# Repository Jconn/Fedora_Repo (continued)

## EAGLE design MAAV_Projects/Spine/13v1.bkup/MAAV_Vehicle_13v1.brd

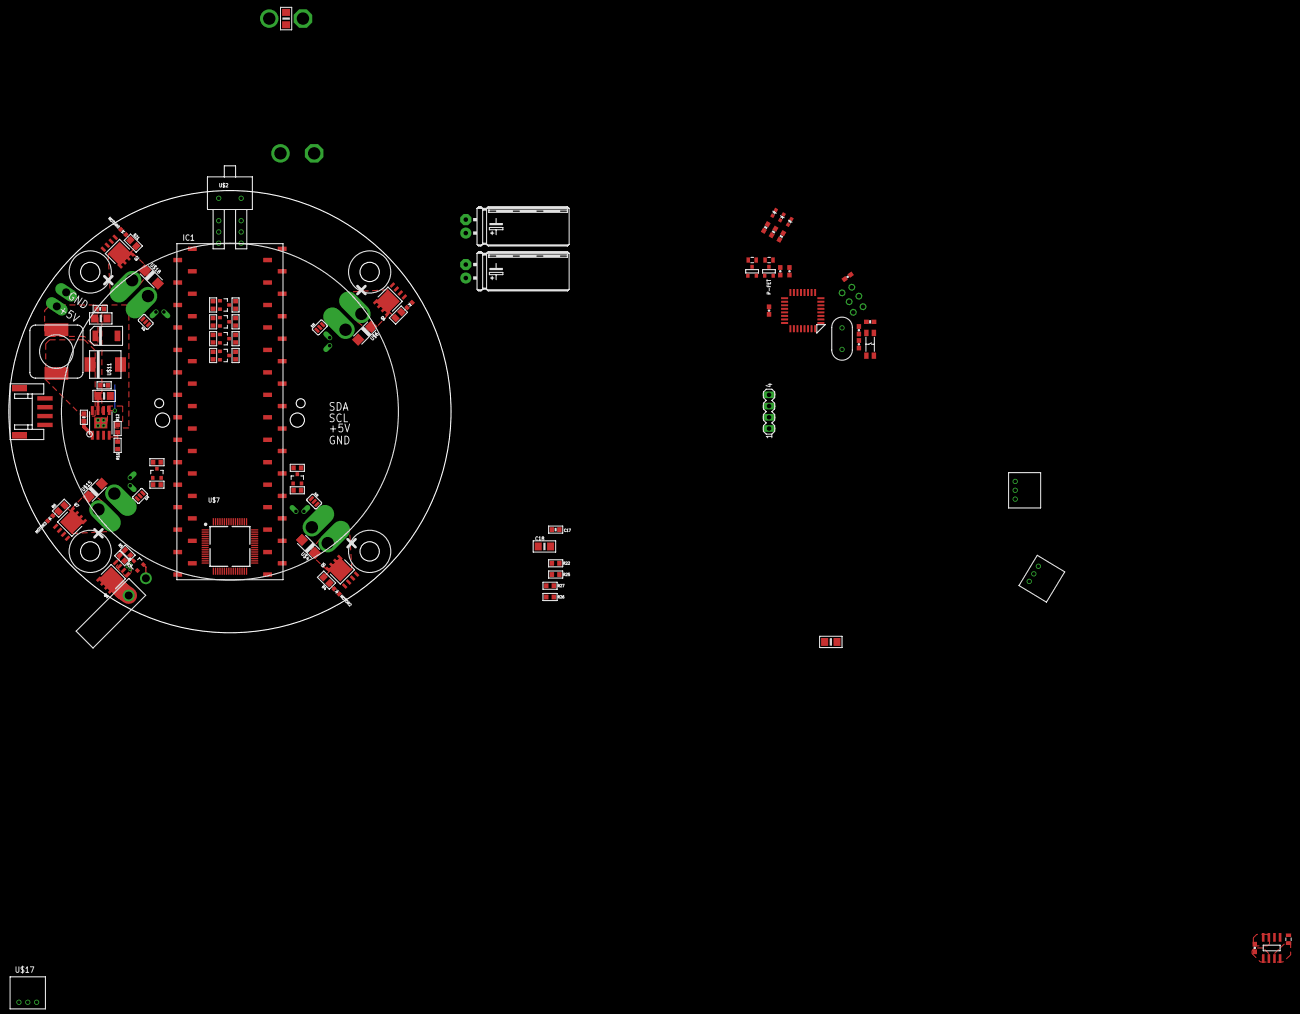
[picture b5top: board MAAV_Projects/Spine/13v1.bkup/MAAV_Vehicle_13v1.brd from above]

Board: 4 copper layers, 100.0 x 100.0 mm, 104 parts (1 on the bottom side), 60 nets.

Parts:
C2: C_2917_POL
C3, C6, C16: 0.01uF; C0603
C4, C5, C7, C18, C25: 10uF; C1206
C8: 10uF; 0805
C9: 10uF; 0603-CAP
C10, C11, C12, C13: 100nF; 0603-CAP
C14, C15: 22pF; 0603-CAP
C17: 0.1uF; C0603
C28, C29: 680uF; EH22-9
IC1: PINTO_SMD
IMU_LAYOUT: IMU
J1: MA03-2
J7: MA04-1; MA-04-SMD
LASER_POWER: POWER_CONN
LED1, LED2, LED3: GREEN; LED-0603
MOTOR0, MOTOR1, MOTOR2, MOTOR3: GREEN; CHIPLED_0603
MR1: SOT-23
Q1: CRYSTAL_16MHZ
Q2, Q4, Q5, Q6, Q7: SO-8_POWER-PAK
Q3: MOSFET-NCHANNELSMD; SOT23-3
R1, R2, R9, R10, R11, R13, R15, R17, R19, R22, R26: 10k; R0603
R3, R5: 1k; R0603
R4, R6, R21, R24: 750; R0805
R7: 10k; 0603-RES
R8, R23: 10k; 0805
R12: 3.16k; R0603
R14, R16, R18, R20: 4.7k; R0603
R25, R27: 432; R0603
R44, R47, R48: 240; 0603-RES
S2: SWITCH-OFF-MOM
SJ1, SJ2, SJ3, SJ4: SJ_3
SV1: MA04-1
T3, T4, T7, T8, T9, T10: MOSFET-NCHANNELSMD; SOT23-3
T11: SOT-23
U2: TPS5450
U3: ATMEGA328-AU; 32-TQFP
U4: REG_3V_8SOIC; 8-SOIC
U$1: INDUCTOR; CDRH127
U$2: SWITCH_DPDT; SWITCH_VERT_DPDT
U$3, U$5, U$13, U$14: ESC_CONN
U$4, U$6, U$15, U$18: DIODE-SCHOTTKY; DO-214AC,SMC
U$7: TM4C123GH6PM; 64-PQFP
U$8: LIPO_POWER
U$9: BATTERY50A; LIPO_POWER_50A
U$10, U$16, U$17: H3894-ND
U$11: DIODE-SCHOTTKYBIG; DO-214AB,SMC
U$12: POWER_HOLES

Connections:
+1V8: IC1.P24, IC1.P34, R1.2, R9.2, R13.2, R15.2, R17.2, R19.2, T3.1, T4.1, T7.1, T8.1, T9.1, T10.1
+5V: C2.A, C7.1, C9.1, C10.1, C11.1, C13.1, C16.1, C17.2, C18.2, IC1.P48, J1.P$6, J7.1, R2.2, R7.2, R10.2, R11.2, R14.2, R16.2, R18.2, R20.2, SV1.2, U3.P$4, U3.P$6, U3.P$18, U4.P$5, U4.P$6, U$1.P2, U$10.POW, U$12.P$1, U$16.POW, U$17.POW
+12V: C3.1, C4.1, C5.1, C25.1, C28.+, C29.+, Q2.S1, Q2.S2, Q2.S3, Q4.S1, Q4.S2, Q4.S3, Q5.S1, Q5.S2, Q5.S3, Q6.S1, Q6.S2, Q6.S3, Q7.S1, Q7.S2, Q7.S3, R3.2, R8.2, U2.P$7, U$2.P$3, U$9.BATT
-3V3: C8.1, U4.P$7, U4.P$8
BATT_SENSE: R26.1, R27.2, U3.P$19
ENABLE: MR1.2, Q3.1, R22.2, R26.2, U$2.P$2
GND: C2.C, C3.2, C4.2, C5.2, C7.2, C8.2, C9.2, C10.2, C11.2, C12.2, C13.2, C14.1, C15.1, C16.2, C17.1, C18.1, C25.2, C28.-, C29.-, IC1.P9, IC1.P23, IC1.P33, IC1.P45, J1.P$4, J7.4, LASER_POWER.P2, LED1.C, LED2.C, LED3.C, MOTOR0.C, MOTOR1.C, MOTOR2.C, MOTOR3.C, Q3.2, R12.2, R23.1, R25.1, R27.1, S2.P$2, S2.P$4, SV1.1, T11.2, U2.P$6, U2.P$9, U2.P$10, U2.P$11, U2.P$12, U2.P$13, U3.P$3, U3.P$5, U3.P$21, U4.P$3, U4.P$4, U$2.P$1, U$2.P$4, U$3.GND, U$4.A, U$5.GND, U$6.A, U$7.P$12, U$7.P$27, U$7.P$39, U$7.P$55, U$9.GND, U$10.GND, U$11.A, U$12.P$2, U$13.GND, U$14.GND, U$15.A, U$16.GND, U$17.GND, U$18.A
KILL_SIG: U3.P$12, U$17.SIG
LED1: R48.2, U3.P$13
LED2: R47.2, U3.P$26
LED3: R44.2, U3.P$2
M0_POWER: Q2.D1, Q2.D2, Q2.D3, Q2.D4, Q2.D5, R21.2, U$13.BATT, U$18.C
M1_POWER: Q6.D1, Q6.D2, Q6.D3, Q6.D4, Q6.D5, R24.2, U$5.BATT, U$6.C
M2_POWER: Q5.D1, Q5.D2, Q5.D3, Q5.D4, Q5.D5, R4.2, U$3.BATT, U$4.C
M3_POWER: Q7.D1, Q7.D2, Q7.D3, Q7.D4, Q7.D5, R6.2, U$14.BATT, U$15.C
MISO: J1.P$1, U3.P$16
MOSI: J1.P$5, U3.P$15
MOTOR0_PWM_1V8: IC1.P38, R13.1, T7.2
MOTOR0_PWM_5V: R14.1, SJ1.3, T7.3
MOTOR1_PWM_1V8: IC1.P36, R15.1, T8.2
MOTOR1_PWM_5V: R16.1, SJ3.3, T8.3
MOTOR2_PWM_1V8: IC1.P35, R17.1, T9.2
MOTOR2_PWM_5V: R18.1, SJ2.3, T9.3
MOTOR3_PWM_1V8: IC1.P37, R19.1, T10.2
MOTOR3_PWM_5V: R20.1, SJ4.3, T10.3
MOTOR_ENABLE: MR1.1, Q2.G, Q5.G, Q6.G, Q7.G, R23.2
MOTOR_LOGIC: T11.3, U3.P$11
unnamed: Q4.G, R3.1, R5.2
unnamed: LED1.A, R44.1
unnamed: C12.1, U3.P$20
unnamed: R11.1, R12.1, U2.P$4
unnamed: MR1.3, R8.1, T11.1
unnamed: C14.2, Q1.P$2, U3.P$8
unnamed: C15.2, Q1.P$1, U3.P$7
unnamed: C6.1, U2.P$1
unnamed: Q3.3, R5.1
unnamed: U2.P$5, U$2.P$5, U$2.P$6
unnamed: MOTOR1.A, R24.1
unnamed: SJ1.2, U$13.SDA/C+
unnamed: MOTOR2.A, R4.1
unnamed: MOTOR3.A, R6.1
unnamed: SJ2.2, U$3.SDA/C+
unnamed: SJ3.2, U$5.SDA/C+
unnamed: SJ4.2, U$14.SDA/C+
unnamed: MOTOR0.A, R21.1
unnamed: C6.2, U2.P$8, U$1.P1, U$11.C
unnamed: LED2.A, R47.1
unnamed: LED3.A, R48.1
unnamed: LASER_POWER.P1, Q4.D1, Q4.D2, Q4.D3, Q4.D4, Q4.D5
unnamed: IC1.P47, R22.1, R25.2
OPT0_SIG: U3.P$23, U$16.SIG
OPT1_SIG: U3.P$1, U$10.SIG
RESET: J1.P$3, R7.1, S2.P$1, S2.P$3, U3.P$29
RXD1: IC1.P17, J7.3
SCK: J1.P$2, U3.P$17
SCL_1V8: IC1.P31, R1.1, T3.2
SCL_5V: R2.1, SV1.4, T3.3, U3.P$28, U$3.SCL/C-, U$5.SCL/C-, U$13.SCL/C-, U$14.SCL/C-
SDA_1V8: IC1.P32, R9.1, T4.2
SDA_5V: R10.1, SJ1.1, SJ2.1, SJ3.1, SJ4.1, SV1.3, T4.3, U3.P$27
TXD1: IC1.P18, J7.2

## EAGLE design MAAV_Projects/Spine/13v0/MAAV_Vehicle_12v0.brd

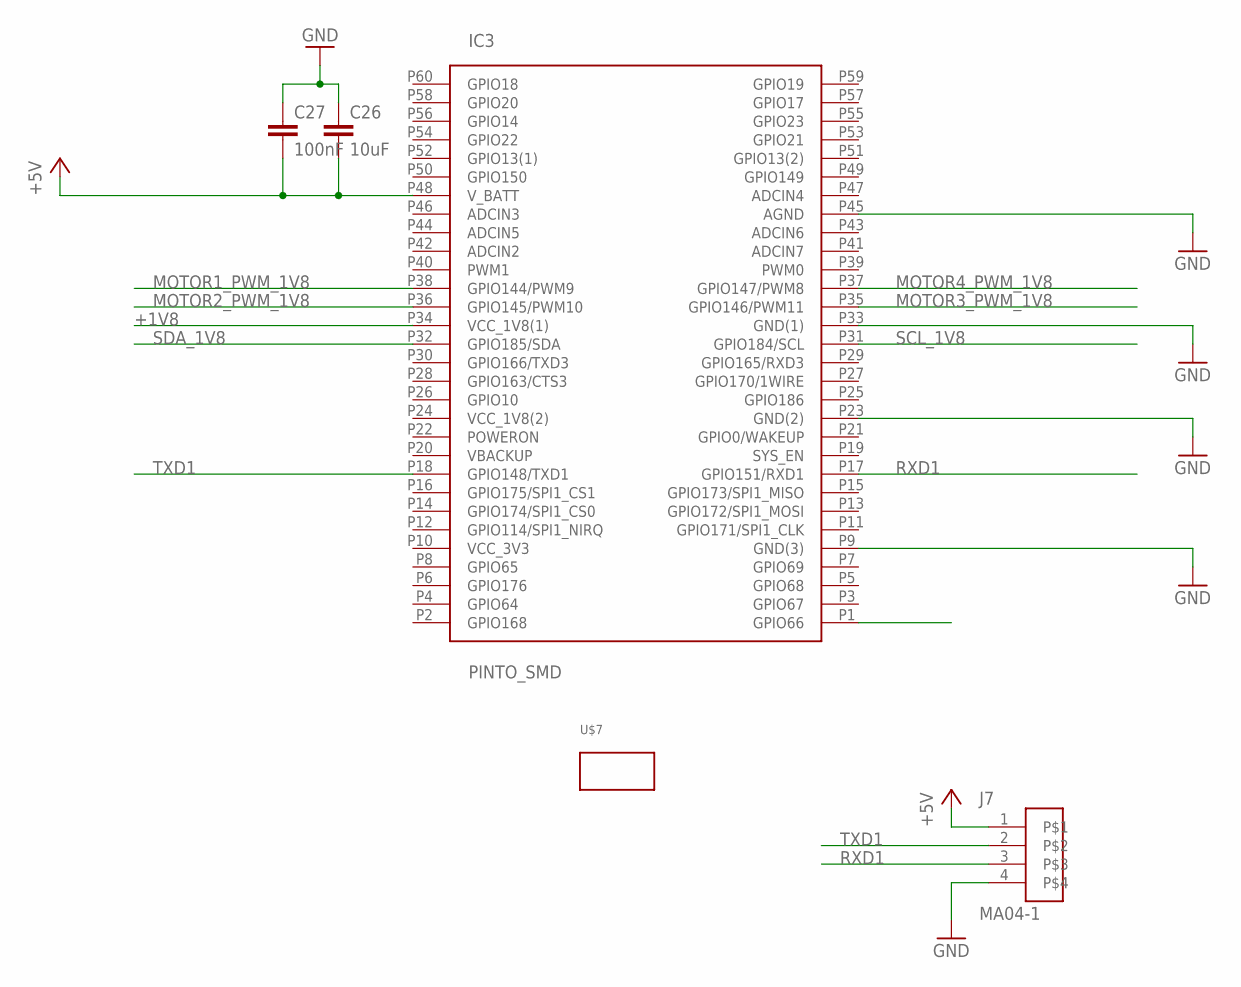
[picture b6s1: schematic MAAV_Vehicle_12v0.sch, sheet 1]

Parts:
C26: 10uF; 0603-CAP; DIGIKEY 445-4112-1-ND
C27: 100nF; 0603-CAP; DIGIKEY 478-1239-1-ND
IC3: PINTO_SMD; DIGIKEY S5641-ND (6)
J7: MA04-1; 455-1751-1-ND
U$7: IMU

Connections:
+1V8: IC3.P34 (VCC_1V8(1)); also elsewhere on the board
+5V: C26.2, C27.2, IC3.P48 (V_BATT), J7.1; also elsewhere on the board
GND: C26.1, C27.1, IC3.P9 (GND(3)), IC3.P23 (GND(2)), IC3.P33 (GND(1)), IC3.P45 (AGND), J7.4; also elsewhere on the board
MOTOR1_PWM_1V8: IC3.P38 (GPIO144/PWM9); also elsewhere on the board
MOTOR2_PWM_1V8: IC3.P36 (GPIO145/PWM10); also elsewhere on the board
MOTOR3_PWM_1V8: IC3.P35 (GPIO146/PWM11); also elsewhere on the board
MOTOR4_PWM_1V8: IC3.P37 (GPIO147/PWM8); also elsewhere on the board
RXD1: IC3.P17 (GPIO151/RXD1), J7.3
SCL_1V8: IC3.P31 (GPIO184/SCL); also elsewhere on the board
SDA_1V8: IC3.P32 (GPIO185/SDA); also elsewhere on the board
TXD1: IC3.P18 (GPIO148/TXD1), J7.2

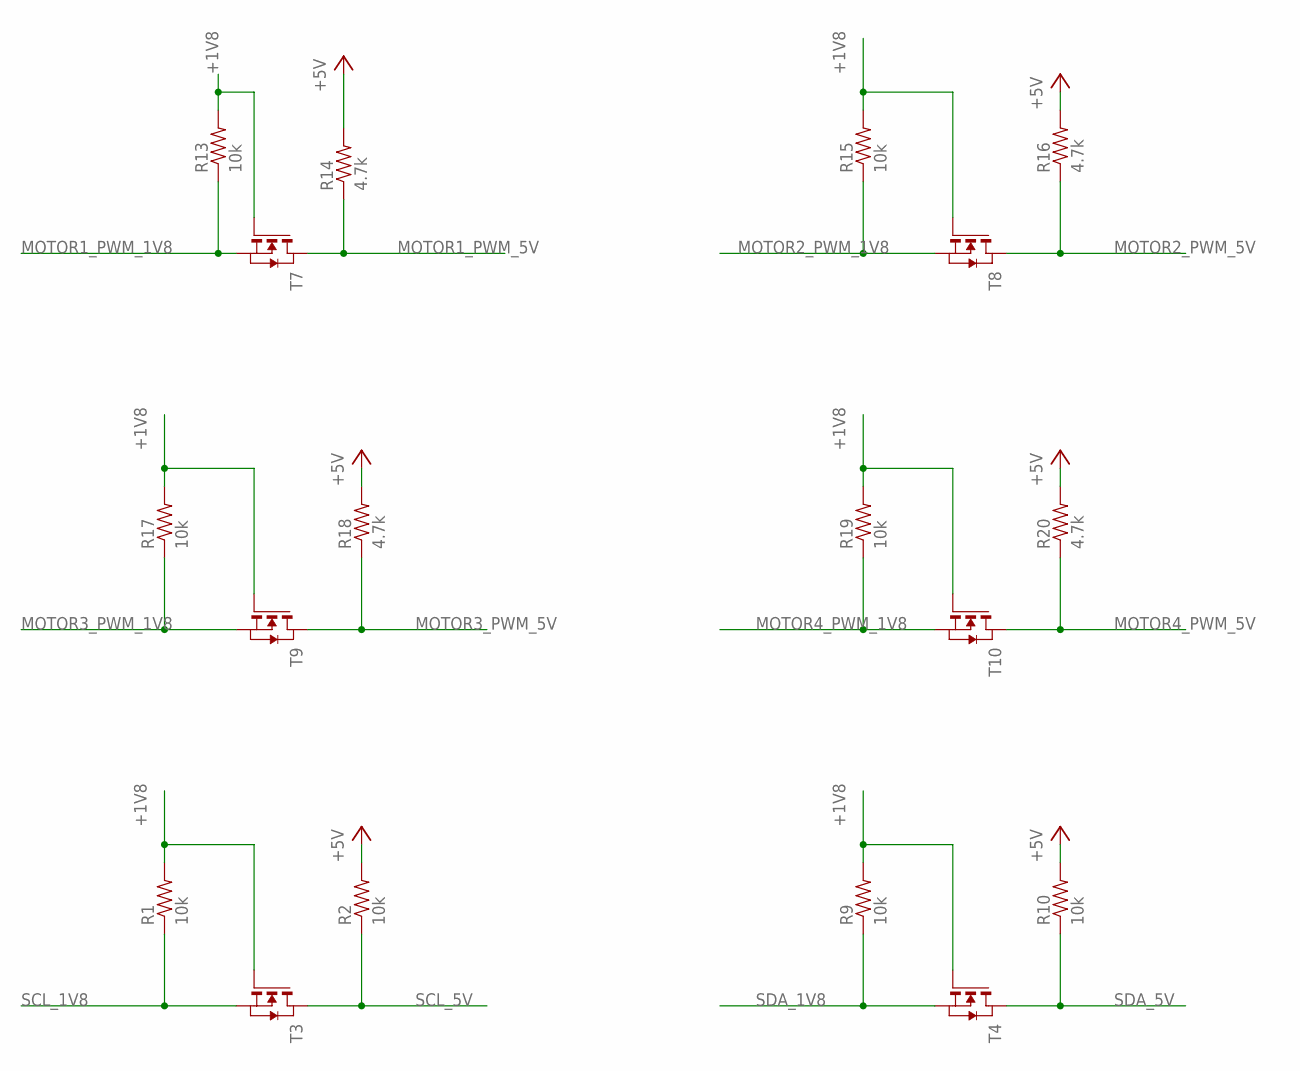
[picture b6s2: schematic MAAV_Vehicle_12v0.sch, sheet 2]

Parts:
R1, R2, R9, R10, R13, R15, R17, R19: 10k; 0603-RES; DIGIKEY P10KGCT-ND
R14, R16, R18, R20: 4.7k; 0603-RES; DIGIKEY P10KGCT-ND
T3, T4, T7, T8, T9, T10: NMOSSOT23; SOT-23; DIGIKEY BSS138KCT-ND

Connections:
+1V8: R1.2, R9.2, R13.2, R15.2, R17.2, R19.2, T3.3 (G), T4.3 (G), T7.3 (G), T8.3 (G), T9.3 (G), T10.3 (G); also elsewhere on the board
+5V: R2.2, R10.2, R14.2, R16.2, R18.2, R20.2; also elsewhere on the board
MOTOR1_PWM_1V8: R13.1, T7.2 (S); also elsewhere on the board
MOTOR1_PWM_5V: R14.1, T7.1 (D); also elsewhere on the board
MOTOR2_PWM_1V8: R15.1, T8.2 (S); also elsewhere on the board
MOTOR2_PWM_5V: R16.1, T8.1 (D); also elsewhere on the board
MOTOR3_PWM_1V8: R17.1, T9.2 (S); also elsewhere on the board
MOTOR3_PWM_5V: R18.1, T9.1 (D); also elsewhere on the board
MOTOR4_PWM_1V8: R19.1, T10.2 (S); also elsewhere on the board
MOTOR4_PWM_5V: R20.1, T10.1 (D); also elsewhere on the board
SCL_1V8: R1.1, T3.2 (S); also elsewhere on the board
SCL_5V: R2.1, T3.1 (D); also elsewhere on the board
SDA_1V8: R9.1, T4.2 (S); also elsewhere on the board
SDA_5V: R10.1, T4.1 (D); also elsewhere on the board

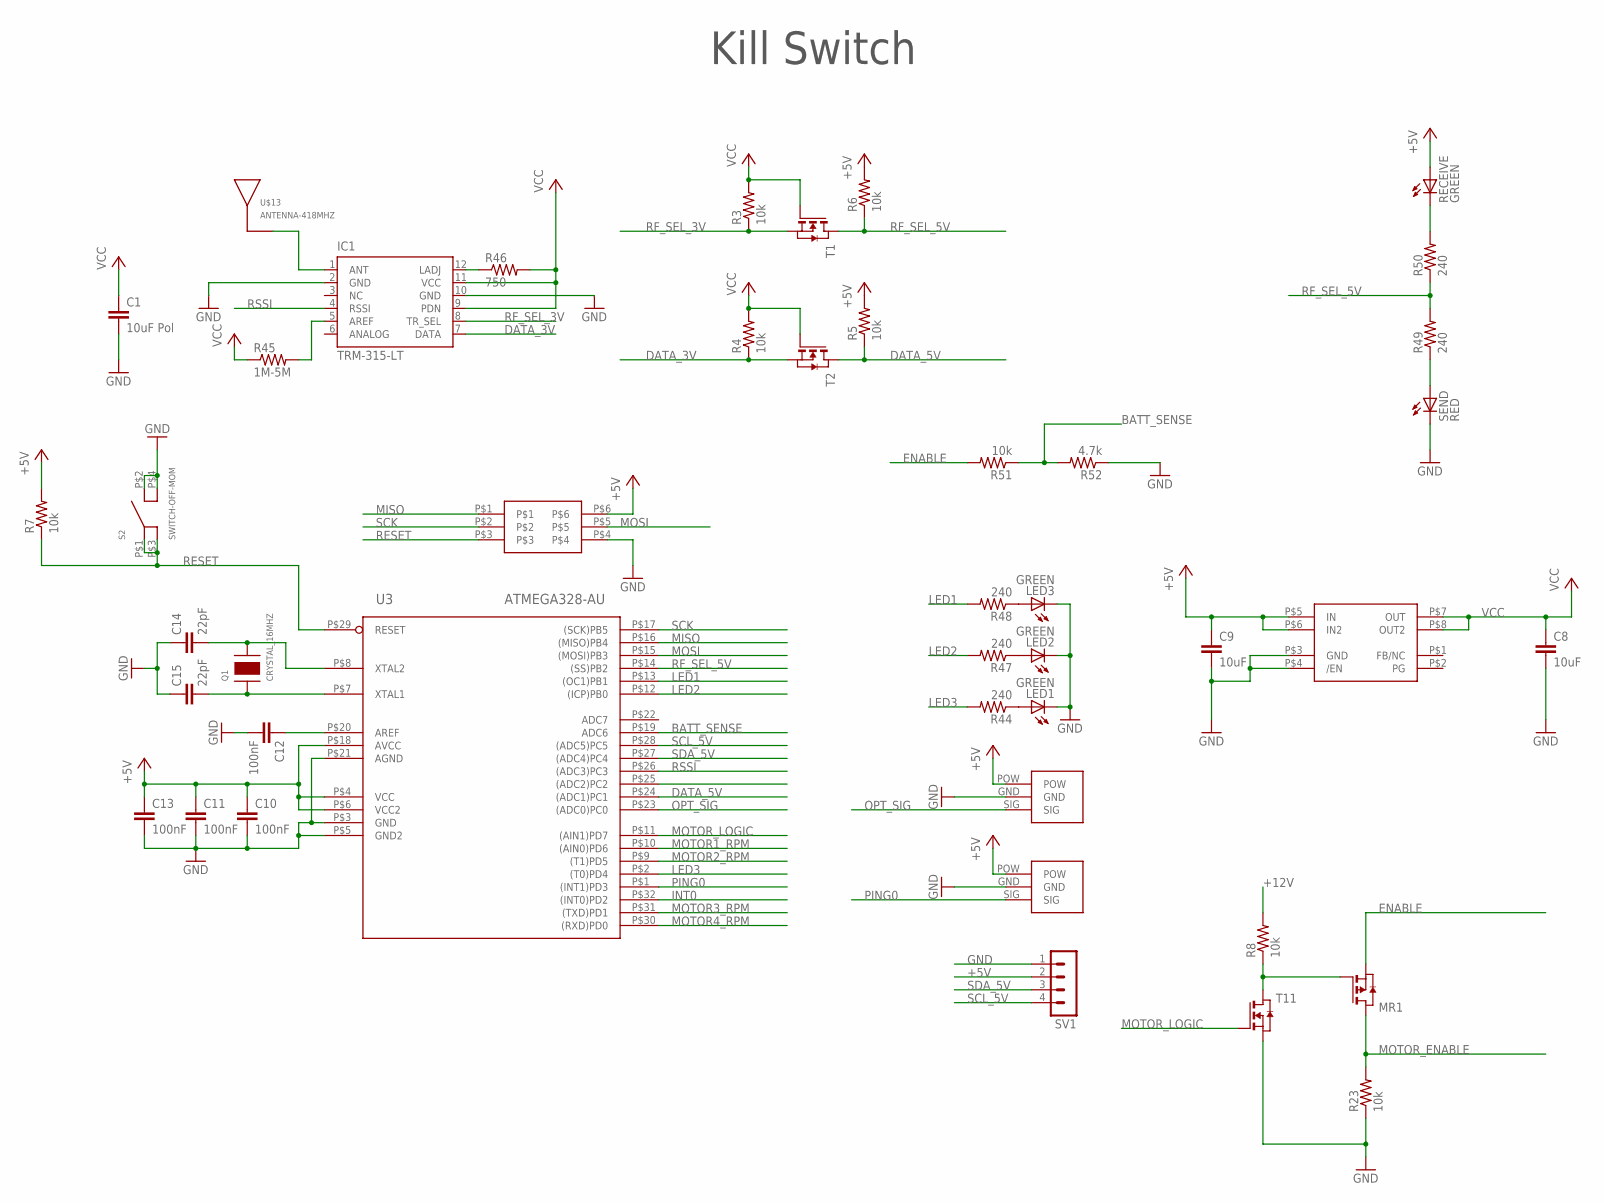
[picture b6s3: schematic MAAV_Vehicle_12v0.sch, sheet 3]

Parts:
C1: 10uF Pol; 0805; DIGIKEY 478-3273-1-ND
C8: 10uF; 0805; DIGIKEY 490-1746-1-ND
C9: 10uF; 0603-CAP; DIGIKEY 445-4112-1-ND
C10, C11, C12, C13: 100nF; 0603-CAP; DIGIKEY 478-1239-1-ND
C14, C15: 22pF; 0603-CAP; DIGIKEY 478-6200-1-ND
IC1: TRM-315-LT; TRM-XXX-LT; DIGIKEY TRM-315-LT-ND
J1: MA03-2
LED1, LED2, LED3: GREEN; LED-0603; DIGIKEY 1080-1405-1-ND
MR1: PMOSSOT23; SOT-23; DIGIKEY FDV304PCT-ND
Q1: CRYSTAL_16MHZ
R3, R4, R5, R6, R7: 10k; 0603-RES; DIGIKEY P10KGCT-ND
R8, R23: 10k; 0805; DIGIKEY P10KACT-ND
R44, R47, R48, R49, R50: 240; 0603-RES; DIGIKEY P240GCT-ND
R45: 1M-5M; 0603-RES; DIGIKEY P1.0MGCT-ND
R46: 750; 0603-RES; DIGIKEY P0.0GCT-ND
R51: 10k; 0603-RES; DIGIKEY P240GCT-ND
R52: 4.7k; 0603-RES; DIGIKEY P4.7KGCT-ND
RECEIVE: GREEN; LED-0603; DIGIKEY 1080-1405-1-ND
S2: SWITCH-OFF-MOM
SEND: RED; LED-0603; DIGIKEY 1080-1400-1-ND
SV1: MA04-1
T1, T2, T11: NMOSSOT23; SOT-23; DIGIKEY BSS138KCT-ND
U3: ATMEGA328-AU; 32-TQFP
U4: REG_3V_8SOIC; 8-SOIC
U$10, U$16: H3894-ND
U$13: ANTENNA-418MHZ

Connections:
+5V: C9.1, C10.1, C11.1, C13.1, J1.P$6, R5.2, R6.2, R7.2, RECEIVE.A, SV1.2, U3.P$4 (VCC), U3.P$6 (VCC2), U3.P$18 (AVCC), U4.P$5 (IN), U4.P$6 (IN2), U$10.POW, U$16.POW; also elsewhere on the board
+12V: R8.2; also elsewhere on the board
ANTENNA: IC1.1 (ANT), U$13.P$1; also elsewhere on the board
BATT_SENSE: R51.1, R52.2, U3.P$19 (ADC6)
DATA_3V: IC1.7 (DATA), R4.1, T2.2 (S)
DATA_5V: R5.1, T2.1 (D), U3.P$24 ((ADC1)PC1)
ENABLE: MR1.2 (S), R51.2; also elsewhere on the board
GND: C1.2, C8.2, C9.2, C10.2, C11.2, C12.2, C13.2, C14.1, C15.1, IC1.2 (GND), IC1.10 (GND), J1.P$4, LED1.C, LED2.C, LED3.C, R23.1, R52.1, S2.P$2 (P2), S2.P$4 (P4), SEND.C, SV1.1, T11.2 (S), U3.P$3 (GND), U3.P$5 (GND2), U3.P$21 (AGND), U4.P$3 (GND), U4.P$4 (/EN), U$10.GND, U$16.GND; also elsewhere on the board
INT0: U3.P$32 ((INT0)PD2); also elsewhere on the board
LED1: R48.2, U3.P$13 ((OC1)PB1)
LED2: R47.2, U3.P$12 ((ICP)PB0)
LED3: R44.2, U3.P$2 ((T0)PD4)
MISO: J1.P$1, U3.P$16 ((MISO)PB4); also elsewhere on the board
MOSI: J1.P$5, U3.P$15 ((MOSI)PB3); also elsewhere on the board
MOTOR1_RPM: U3.P$10 ((AIN0)PD6); also elsewhere on the board
MOTOR2_RPM: U3.P$9 ((T1)PD5); also elsewhere on the board
MOTOR3_RPM: U3.P$31 ((TXD)PD1); also elsewhere on the board
MOTOR4_RPM: U3.P$30 ((RXD)PD0); also elsewhere on the board
MOTOR_ENABLE: MR1.1 (D), R23.2; also elsewhere on the board
MOTOR_LOGIC: T11.3 (G), U3.P$11 ((AIN1)PD7)
unnamed: LED1.A, R44.1
unnamed: C12.1, U3.P$20 (AREF)
unnamed: MR1.3 (G), R8.1, T11.1 (D)
unnamed: C14.2, Q1.P$2, U3.P$8 (XTAL2)
unnamed: C15.2, Q1.P$1, U3.P$7 (XTAL1)
unnamed: R50.2, RECEIVE.C
unnamed: R49.1, SEND.A
unnamed: IC1.5 (AREF), R45.2
unnamed: IC1.12 (LADJ), R46.1
unnamed: LED2.A, R47.1
unnamed: LED3.A, R48.1
OPT_SIG: U3.P$23 ((ADC0)PC0), U$16.SIG
PING0: U3.P$1 ((INT1)PD3), U$10.SIG
RESET: J1.P$3, R7.1, S2.P$1 (P1), S2.P$3 (P3), U3.P$29 (RESET)
RF_SEL_3V: IC1.8 (TR_SEL), R3.1, T1.2 (S)
RF_SEL_5V: R6.1, R49.2, R50.1, T1.1 (D), U3.P$14 ((SS)PB2); also elsewhere on the board
RSSI: IC1.4 (RSSI), U3.P$26 ((ADC3)PC3)
SCK: J1.P$2, U3.P$17 ((SCK)PB5); also elsewhere on the board
SCL_5V: SV1.4, U3.P$28 ((ADC5)PC5); also elsewhere on the board
SDA_5V: SV1.3, U3.P$27 ((ADC4)PC4); also elsewhere on the board
VCC: C1.1, C8.1, IC1.9 (PDN), IC1.11 (VCC), R3.2, R4.2, R45.1, R46.2, T1.3 (G), T2.3 (G), U4.P$7 (OUT), U4.P$8 (OUT2)

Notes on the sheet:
Kill Switch

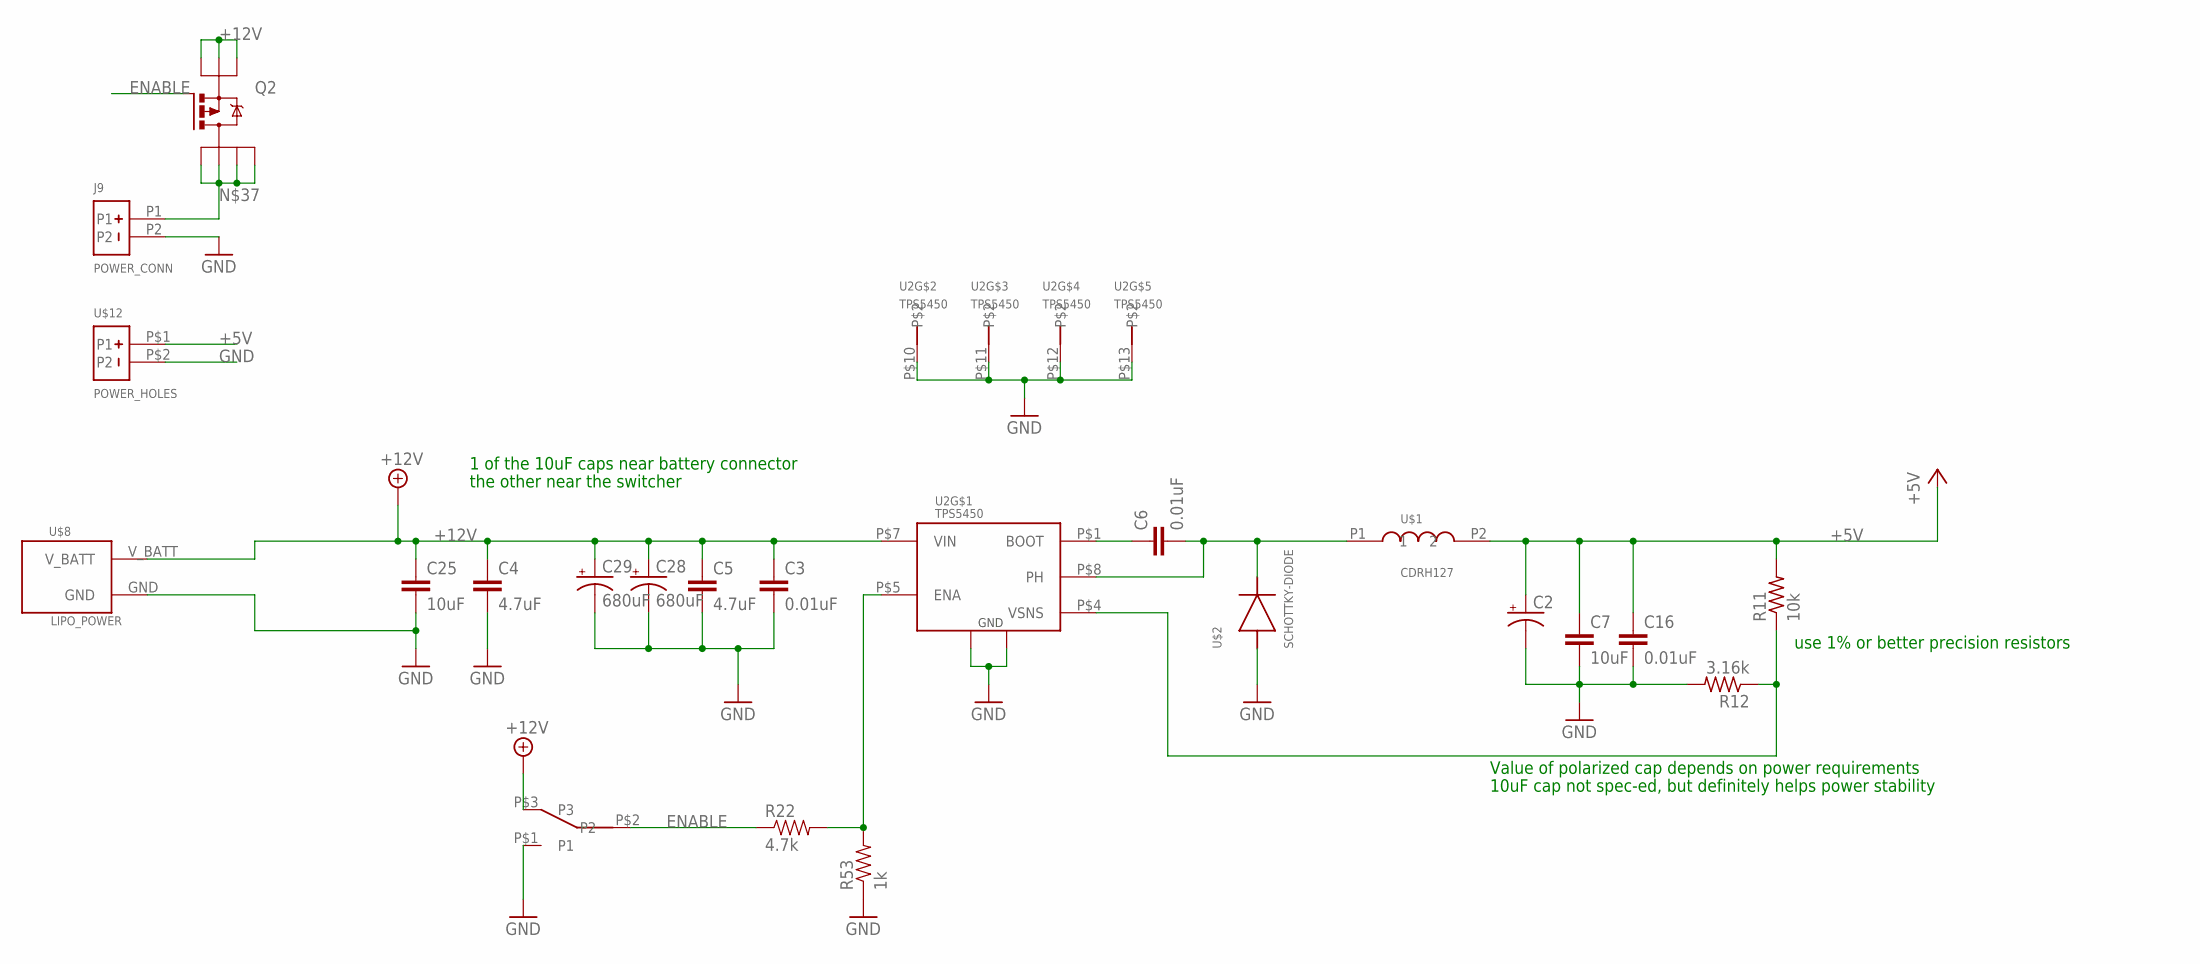
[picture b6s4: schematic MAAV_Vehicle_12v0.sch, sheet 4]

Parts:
C2: CAP_POL; 2917; DIGIKEY 478-1811-1-ND
C3, C6, C16: 0.01uF; C1210; DIGIKEY 478-1601-1-ND
C4, C5: 4.7uF; C1210; DIGIKEY 399-5777-1-ND
C7, C25: 10uF; C1210; DIGIKEY 445-1597-1-ND
C28, C29: 680uF; EH22-9; DIGIKEY P12378-ND
J9: POWER_CONN
Q2: P-MOSFET-SO8; SO-08; DIGIKEY SI4114DY-T1-GE3CT-ND
R11: 10k; R0603; DIGIKEY P10KDBCT-ND
R12: 3.16k; R0603; DIGIKEY 311-3.16KDCT-ND
R22: 4.7k; 0805; DIGIKEY P4.7KACT-ND
R53: 1k; 0805; DIGIKEY P1.0KACT-ND
S1: SWITCH-ON-ON
U2: TPS5450
U$1: CDRH127
U$2: SCHOTTKY-DIODE; DO-214AB,SMC; DIGIKEY B540C-FDICT-ND
U$8: LIPO_POWER
U$12: POWER_HOLES

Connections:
+5V: C2.2 (+), C7.1, C16.1, R11.2, U$1.P2 (2), U$12.P$1 (P1); also elsewhere on the board
+12V: C3.1, C4.1, C5.1, C25.1, C28.+, C29.+, Q2.1 (S), Q2.2 (S), Q2.3 (S), S1.P$3 (P3), U2.P$7 (VIN), U$8.V_BATT; also elsewhere on the board
ENABLE: Q2.4 (G), R22.1, S1.P$2 (P2); also elsewhere on the board
GND: C2.1 (-), C3.2, C4.2, C5.2, C7.2, C16.2, C25.2, C28.-, C29.-, J9.P2, R12.2, R53.1, S1.P$1 (P1), U2.P$6 (GND), U2.P$9 (PGND), U2.P$10, U2.P$11, U2.P$12, U2.P$13, U$2.P$1, U$8.GND, U$12.P$2 (P2); also elsewhere on the board
unnamed: R11.1, R12.1, U2.P$4 (VSNS)
unnamed: C6.1, U2.P$1 (BOOT)
unnamed: R22.2, R53.2, U2.P$5 (ENA)
unnamed: C6.2, U2.P$8 (PH), U$1.P1 (1), U$2.P$2
unnamed: J9.P1, Q2.5 (D), Q2.6 (D), Q2.7 (D), Q2.8 (D)

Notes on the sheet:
Value of polarized cap depends on power requirements
10uF cap not spec-ed, but definitely helps power stability
1 of the 10uF caps near battery connector
the other near the switcher
use 1% or better precision resistors

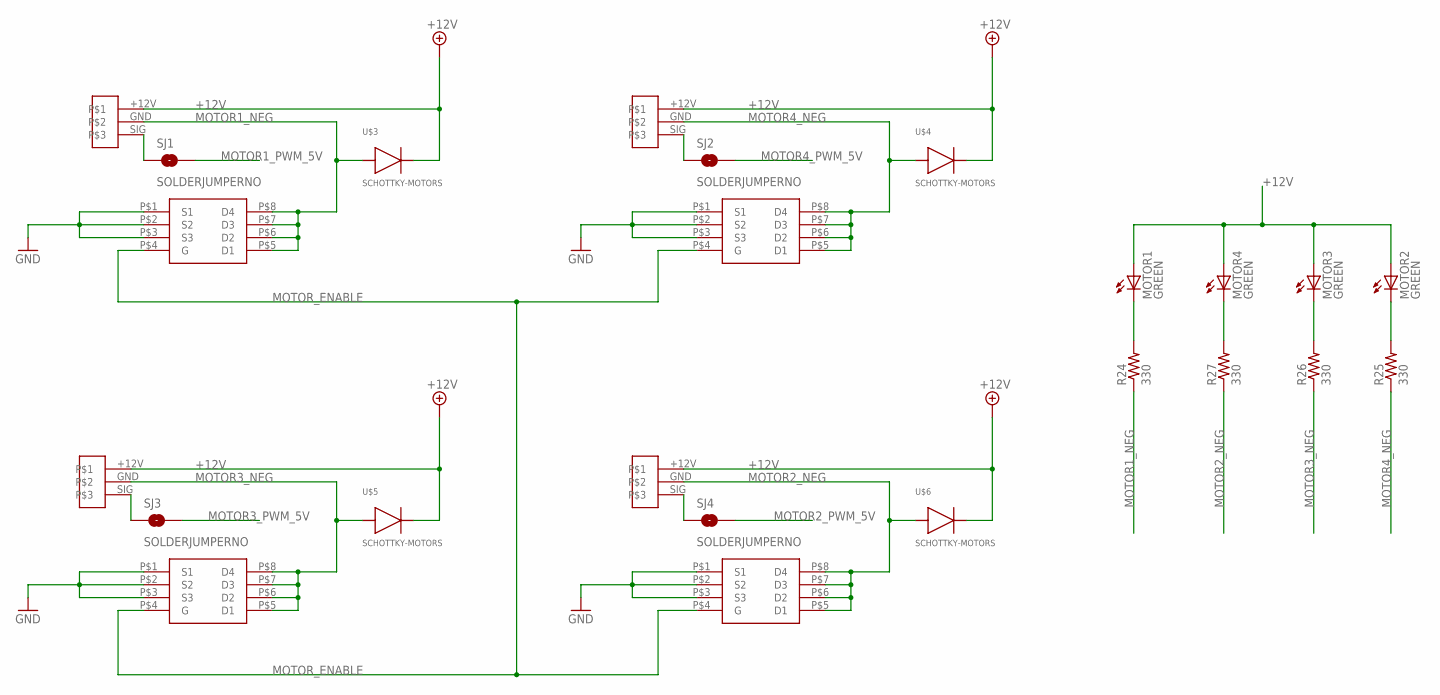
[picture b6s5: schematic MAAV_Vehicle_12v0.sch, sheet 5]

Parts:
J2, J3, J4, J5: MOTOR_CONNTRU_HOLE; MOTOR_CONN_THRU
MOTOR1, MOTOR2, MOTOR3, MOTOR4: GREEN; CHIPLED_0805; DIGIKEY 160-1423-1-ND
R24, R25, R26, R27: 330; 0805; DIGIKEY P330ADCT-ND
SJ1, SJ2, SJ3, SJ4: SOLDERJUMPERNO; SJ_2S-NO
T5, T6, T12, T13: MOTOR_NFET; 8-SOIC
U$3, U$4, U$5, U$6: SCHOTTKY-MOTORS; DO-214AC,SMA

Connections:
+12V: J2.+12V, J3.+12V, J4.+12V, J5.+12V, MOTOR1.A, MOTOR2.A, MOTOR3.A, MOTOR4.A, U$3.P$2, U$4.P$2, U$5.P$2, U$6.P$2; also elsewhere on the board
GND: T5.P$1 (S1), T5.P$2 (S2), T5.P$3 (S3), T6.P$1 (S1), T6.P$2 (S2), T6.P$3 (S3), T12.P$1 (S1), T12.P$2 (S2), T12.P$3 (S3), T13.P$1 (S1), T13.P$2 (S2), T13.P$3 (S3); also elsewhere on the board
MOTOR1_NEG: J2.GND, R24.1, T5.P$5 (D1), T5.P$6 (D2), T5.P$7 (D3), T5.P$8 (D4), U$3.P$1
MOTOR1_PWM_5V: SJ1.2; also elsewhere on the board
MOTOR2_NEG: J5.GND, R27.1, T13.P$5 (D1), T13.P$6 (D2), T13.P$7 (D3), T13.P$8 (D4), U$6.P$1
MOTOR2_PWM_5V: SJ4.2; also elsewhere on the board
MOTOR3_NEG: J3.GND, R26.1, T12.P$5 (D1), T12.P$6 (D2), T12.P$7 (D3), T12.P$8 (D4), U$5.P$1
MOTOR3_PWM_5V: SJ3.2; also elsewhere on the board
MOTOR4_NEG: J4.GND, R25.1, T6.P$5 (D1), T6.P$6 (D2), T6.P$7 (D3), T6.P$8 (D4), U$4.P$1
MOTOR4_PWM_5V: SJ2.2; also elsewhere on the board
MOTOR_ENABLE: T5.P$4 (G), T6.P$4 (G), T12.P$4 (G), T13.P$4 (G); also elsewhere on the board
unnamed: MOTOR1.C, R24.2
unnamed: MOTOR2.C, R25.2
unnamed: MOTOR3.C, R26.2
unnamed: MOTOR4.C, R27.2
unnamed: J2.SIG, SJ1.1
unnamed: J5.SIG, SJ4.1
unnamed: J4.SIG, SJ2.1
unnamed: J3.SIG, SJ3.1

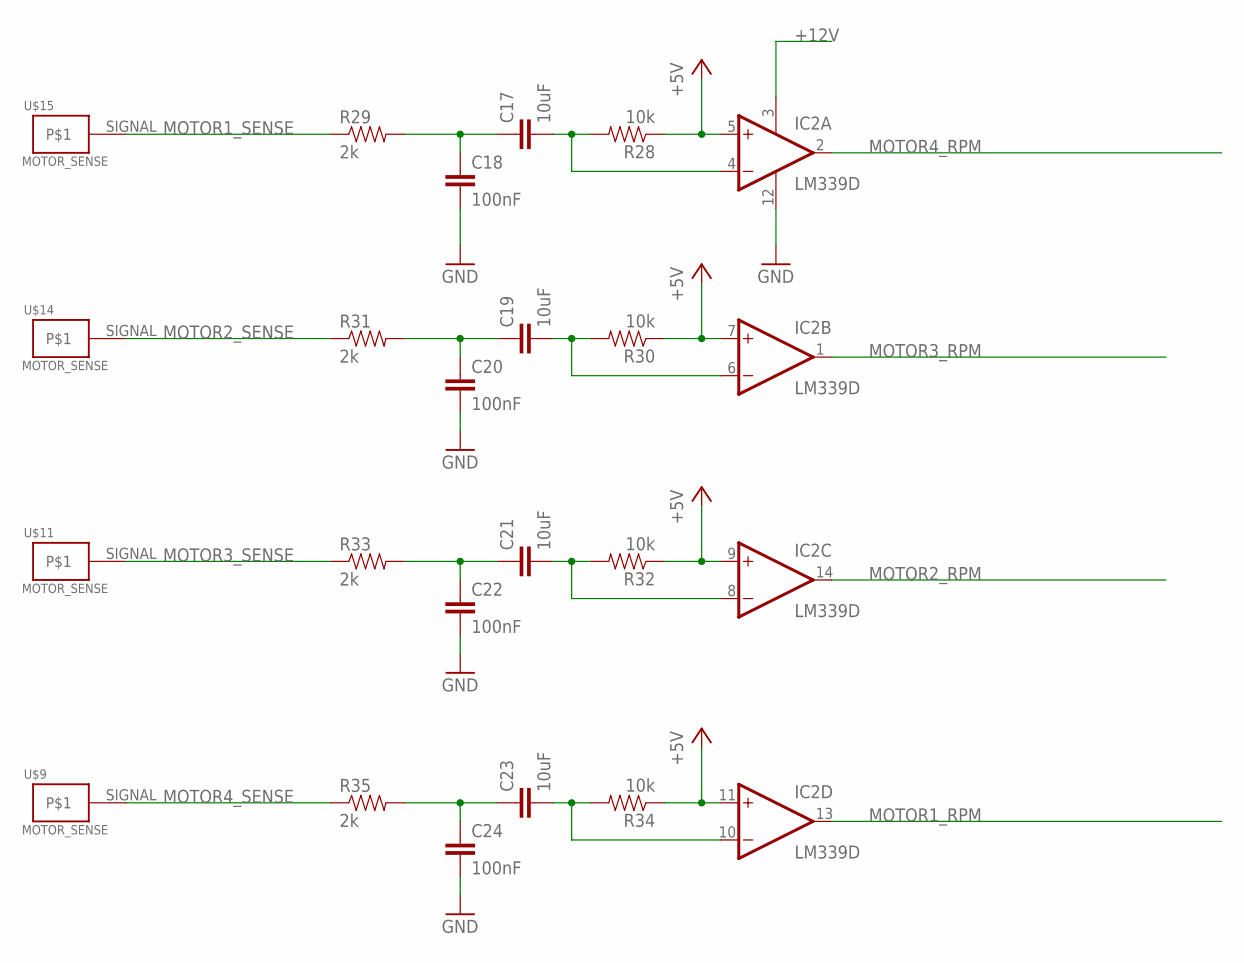
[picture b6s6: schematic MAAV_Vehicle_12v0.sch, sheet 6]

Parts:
C17, C19, C21, C23: 10uF; 0603-CAP; DIGIKEY 445-4112-1-ND
C18, C20, C22, C24: 100nF; 0603-CAP; DIGIKEY 478-1239-1-ND
IC2: LM339D; SO14; DIGIKEY 296-1013-1-ND
R28, R30, R32, R34: 10k; 0603-RES; DIGIKEY P10KGCT-ND
R29, R31, R33, R35: 2k; 0603-RES; DIGIKEY P2.0KGCT-ND
U$9, U$11, U$14, U$15: MOTOR_SENSE

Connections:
+5V: IC2.5 (+IN), IC2.7 (+IN), IC2.9 (+IN), IC2.11 (+IN), R28.1, R30.1, R32.1, R34.1; also elsewhere on the board
+12V: IC2.3 (V+); also elsewhere on the board
GND: C18.2, C20.2, C22.2, C24.2, IC2.12 (GND); also elsewhere on the board
MOTOR1_RPM: IC2.13 (OUT); also elsewhere on the board
MOTOR1_SENSE: R29.1, U$15.SIGNAL
MOTOR2_RPM: IC2.14 (OUT); also elsewhere on the board
MOTOR2_SENSE: R31.1, U$14.SIGNAL
MOTOR3_RPM: IC2.1 (OUT); also elsewhere on the board
MOTOR3_SENSE: R33.1, U$11.SIGNAL
MOTOR4_RPM: IC2.2 (OUT); also elsewhere on the board
MOTOR4_SENSE: R35.1, U$9.SIGNAL
unnamed: C19.1, C20.1, R31.2
unnamed: C17.2, IC2.4 (-IN), R28.2
unnamed: C17.1, C18.1, R29.2
unnamed: C19.2, IC2.6 (-IN), R30.2
unnamed: C21.1, C22.1, R33.2
unnamed: C21.2, IC2.8 (-IN), R32.2
unnamed: C23.1, C24.1, R35.2
unnamed: C23.2, IC2.10 (-IN), R34.2

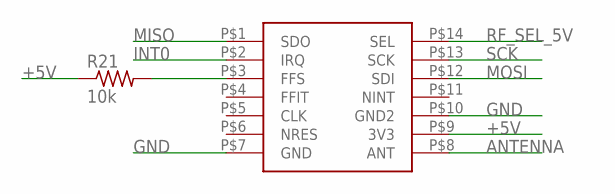
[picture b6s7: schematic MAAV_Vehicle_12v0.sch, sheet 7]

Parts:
R21: 10k; R0603
U$17: RF12

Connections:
+5V: R21.1, U$17.P$9 (3V3); also elsewhere on the board
ANTENNA: U$17.P$8 (ANT); also elsewhere on the board
GND: U$17.P$7 (GND), U$17.P$10 (GND2); also elsewhere on the board
INT0: U$17.P$2 (IRQ); also elsewhere on the board
MISO: U$17.P$1 (SDO); also elsewhere on the board
MOSI: U$17.P$12 (SDI); also elsewhere on the board
unnamed: R21.2, U$17.P$3 (FFS)
RF_SEL_5V: U$17.P$14 (SEL); also elsewhere on the board
SCK: U$17.P$13 (SCK); also elsewhere on the board

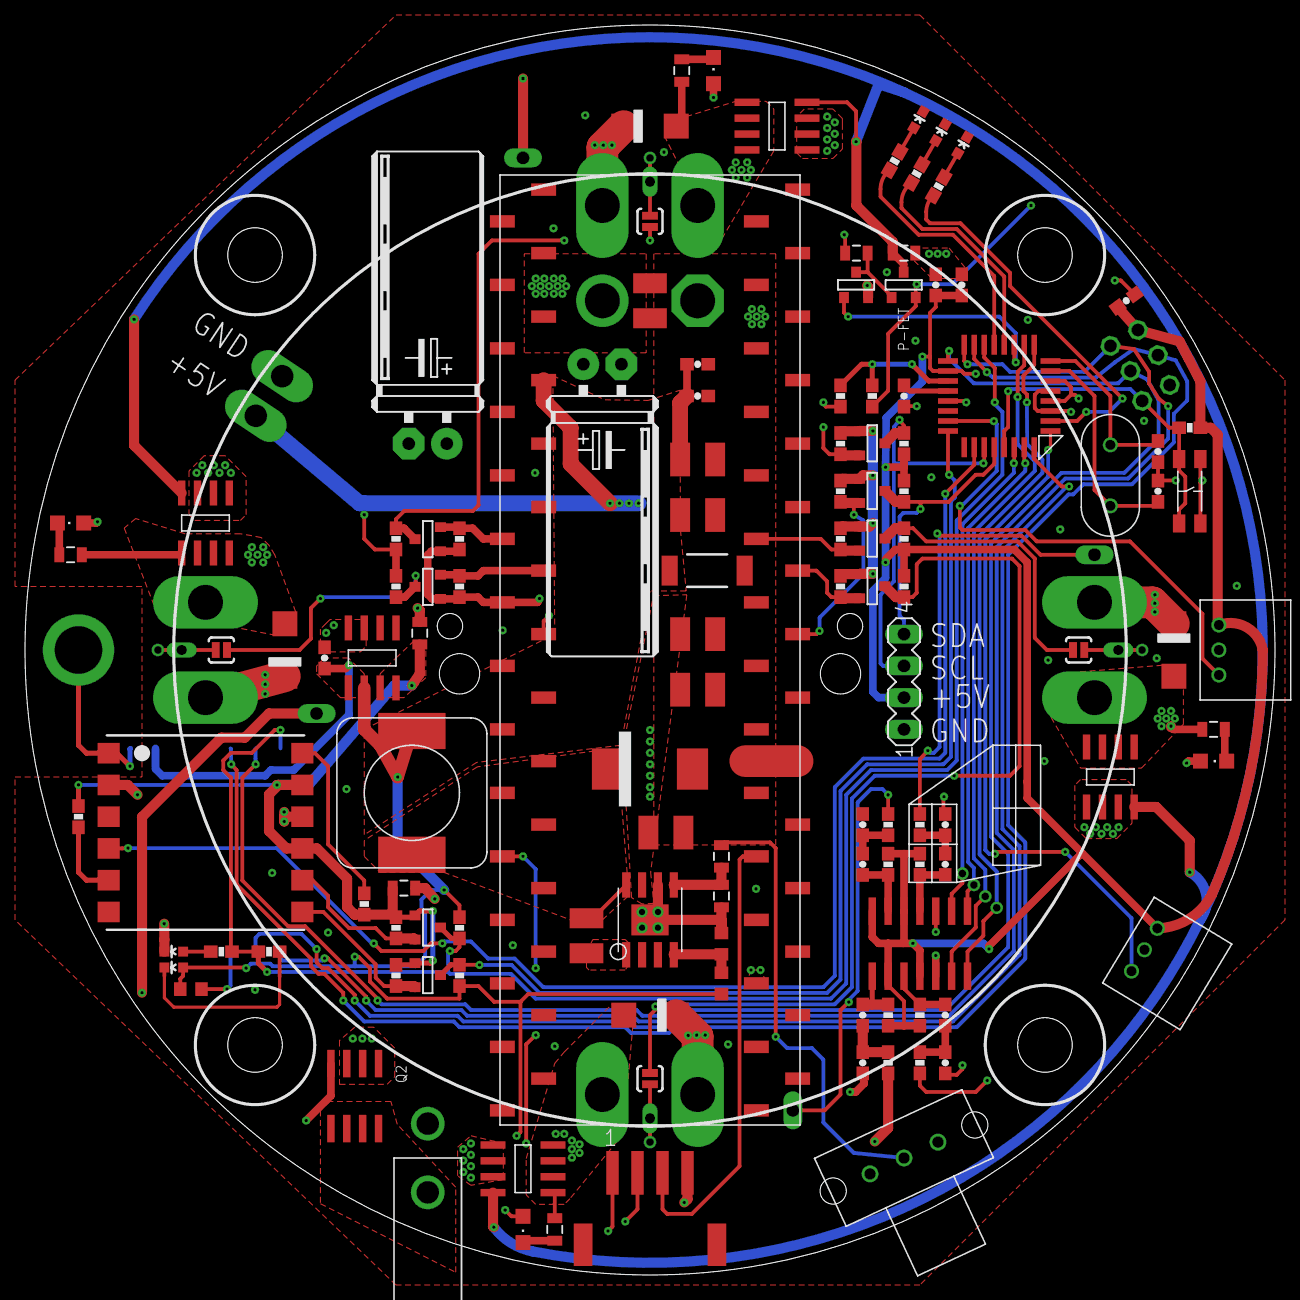
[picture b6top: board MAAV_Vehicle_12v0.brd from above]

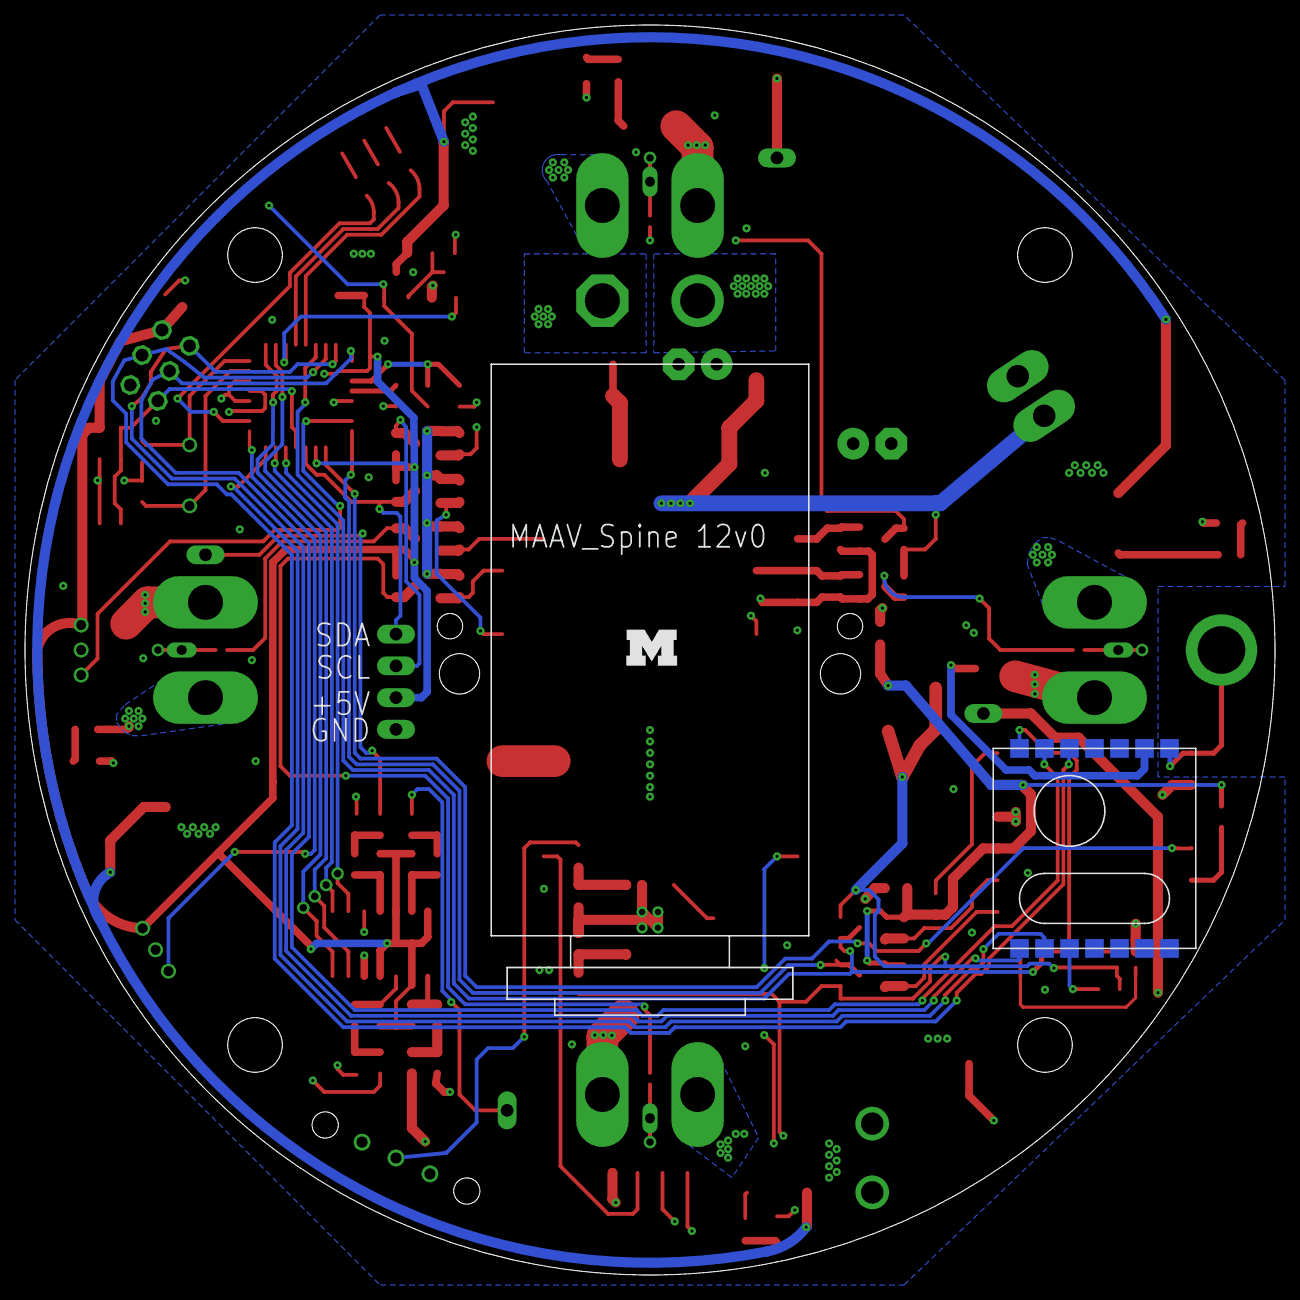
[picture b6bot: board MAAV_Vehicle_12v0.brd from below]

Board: 4 copper layers, 100.0 x 100.0 mm, 137 parts (3 on the bottom side), 84 nets.

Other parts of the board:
U$18: BLOCK-M
